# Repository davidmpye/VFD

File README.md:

This repository contains a design for an IV-11 based Vacuum Fluorescent Display (VFD) display unit.

Key points of the design:

* Support for 8 tubes (can install only 6 if you want the traditional 2-2-2 clock display)
* Can daisy chain boards to make longer displays
* Wifi capable (MQTT etc? - firmware doesn't yet enable this)
* Runs off a 5V 2A supply (USB B socket)
* Four buttons for setting time/other functions

Parts count/prices kept down by using 'generic' ebay modules to provide:

* DS3231 Real Time Clock (battery backed)
* Boost converter module to provide the ~25VDC to power the VFD
* Buck converter module to provide 1.5v to heat the cathodes
* Wemos D1 Mini board to provide the brains
* 5mm encapsulated addressable RGB LEDs to provide the colour effects.

Please see the project wiki for more details.

https://github.com/davidmpye/VFD/wiki

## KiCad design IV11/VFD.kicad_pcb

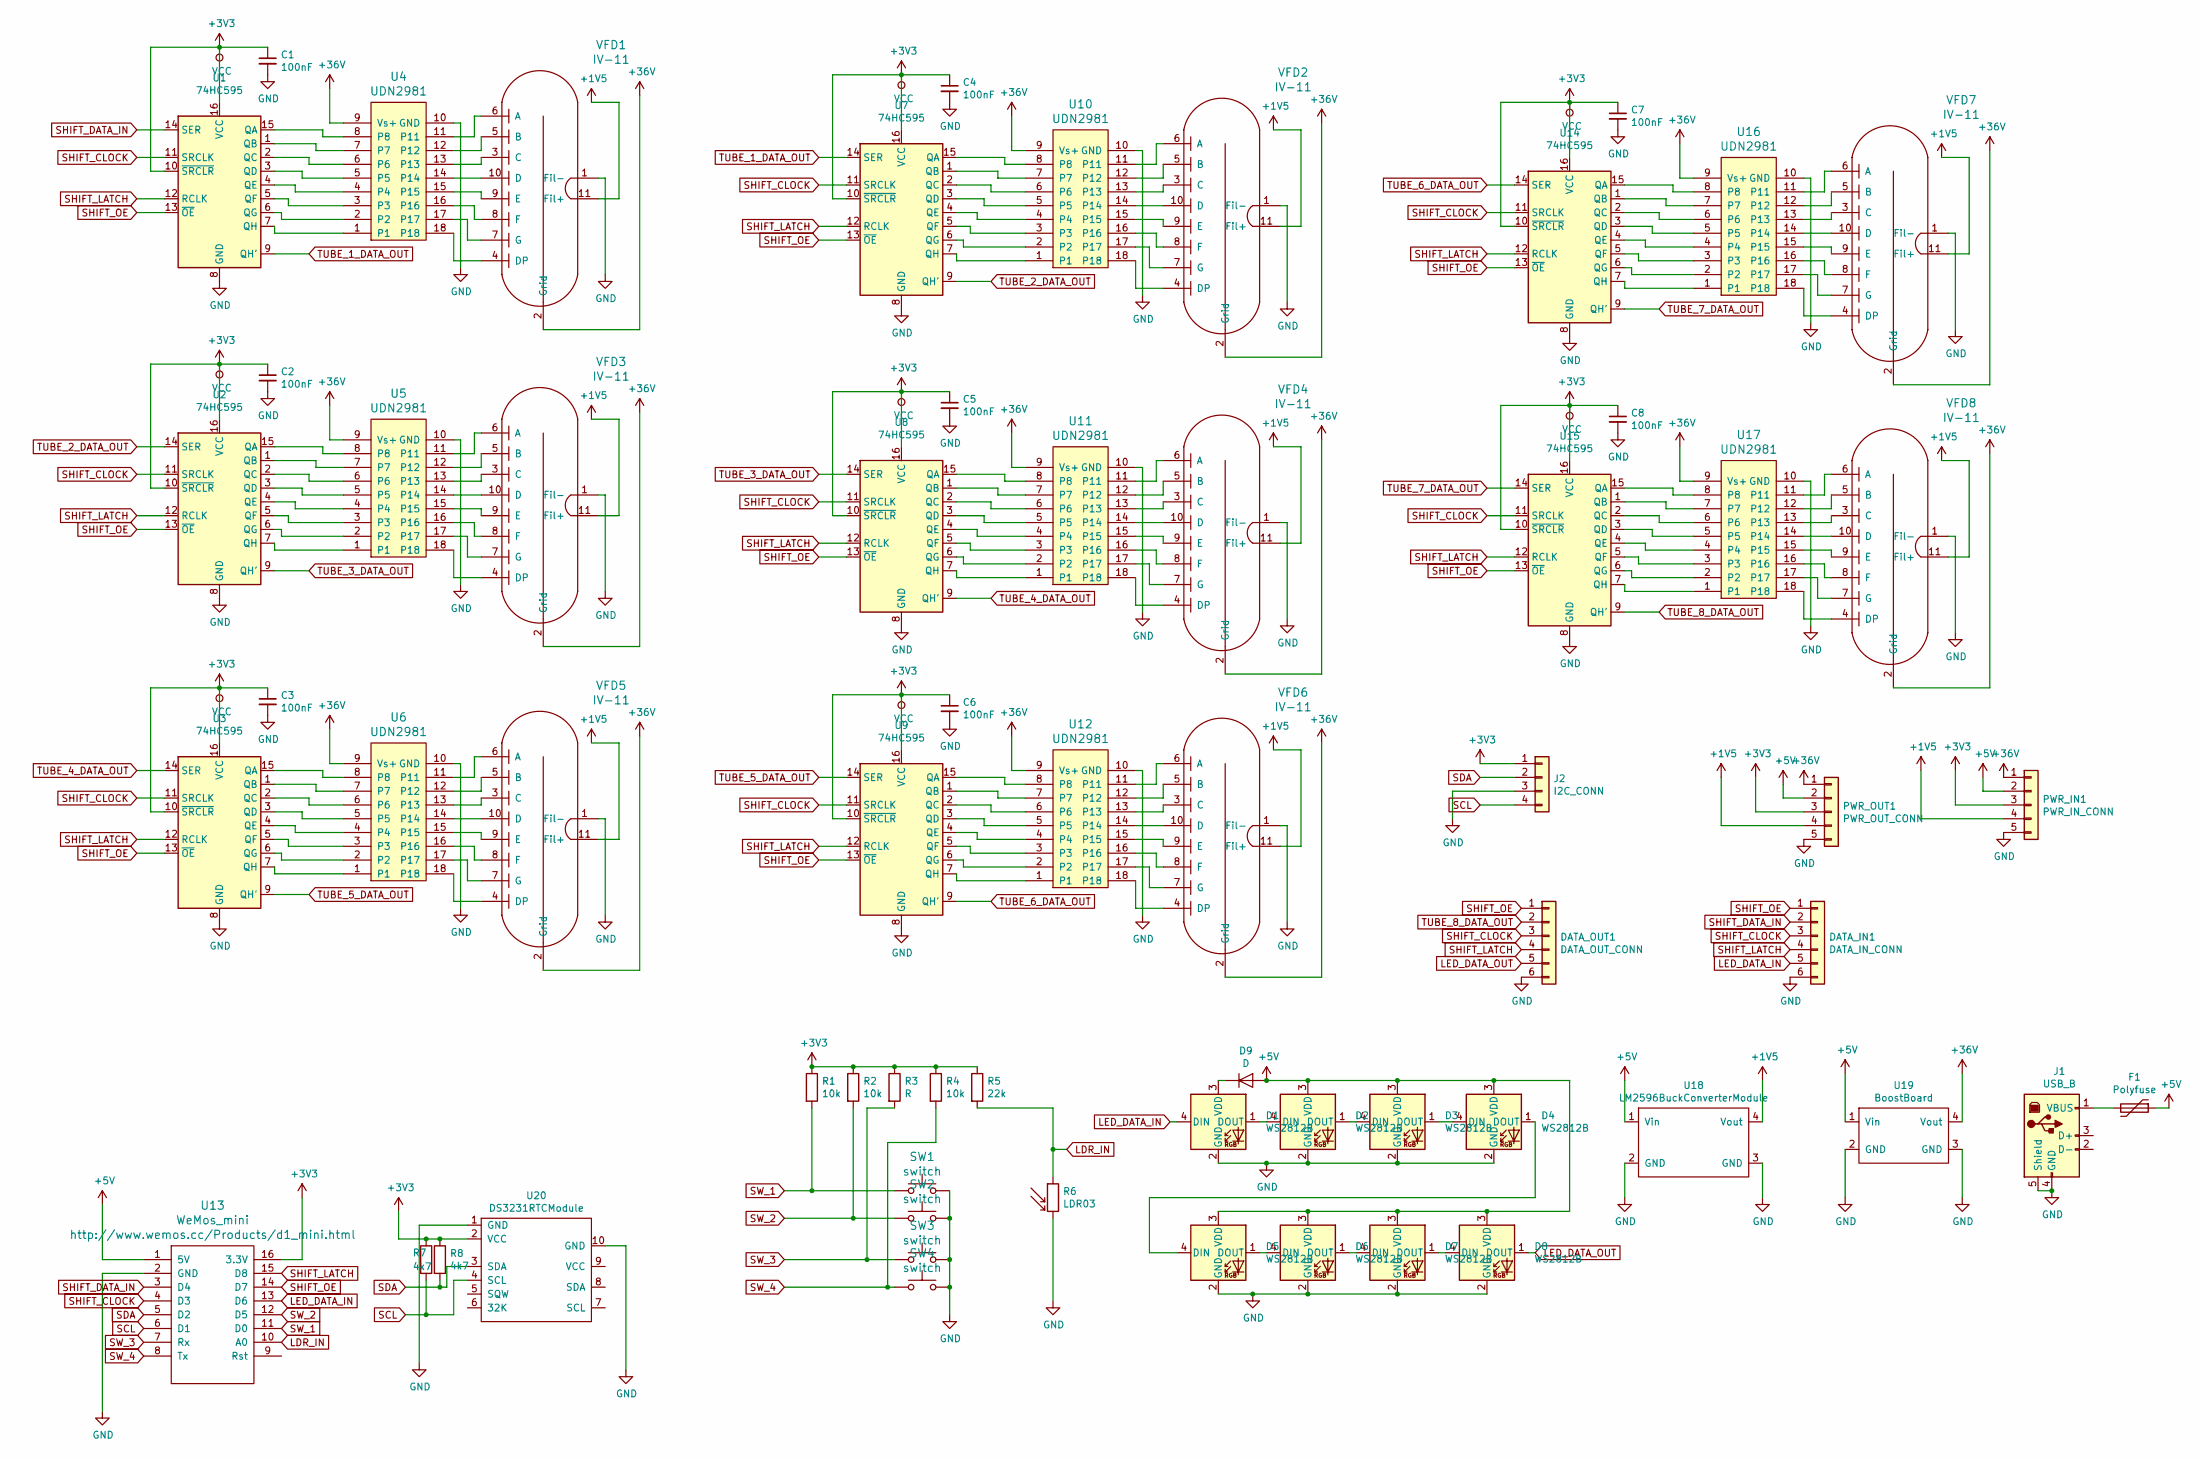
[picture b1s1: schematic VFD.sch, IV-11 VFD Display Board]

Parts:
C1, C2, C3, C4, C5, C6, C7, C8: 100nF; C_Disc_D7.0mm_W2.5mm_P5.00mm
D1, D2, D3, D4, D5, D6, D7, D8: WS2812B; LED_D5.0mm-4-Wide
D9: D; D_DO-35_SOD27_P7.62mm_Horizontal
DATA_IN1: DATA_IN_CONN; PinSocket_1x06_P2.54mm_Horizontal
DATA_OUT1: DATA_OUT_CONN; PinHeader_1x06_P2.54mm_Horizontal
F1: Polyfuse; R_Axial_DIN0309_L9.0mm_D3.2mm_P15.24mm_Horizontal
J1: USB_B; USB_B_OST_USB-B1HSxx_Horizontal
J2: I2C_CONN; PinHeader_1x04_P2.54mm_Horizontal
PWR_IN1: PWR_IN_CONN; PinSocket_1x05_P2.54mm_Horizontal
PWR_OUT1: PWR_OUT_CONN; PinHeader_1x05_P2.54mm_Horizontal
R1, R2, R4: 10k; R_Axial_DIN0411_L9.9mm_D3.6mm_P12.70mm_Horizontal
R3: R; R_Axial_DIN0411_L9.9mm_D3.6mm_P12.70mm_Horizontal
R5: 22k; R_Axial_DIN0411_L9.9mm_D3.6mm_P12.70mm_Horizontal
R6: LDR03; R_LDR_10x8.5mm_P7.6mm_Vertical
R7, R8: 4k7; R_Axial_DIN0411_L9.9mm_D3.6mm_P12.70mm_Horizontal
SW1, SW2, SW3, SW4: switch; SW_Tactile_SKHH_Angled
U1, U2, U3, U7, U8, U9, U14, U15: 74HC595; DIP-16_W7.62mm_Socket_LongPads
U4, U5, U6, U10, U11, U12, U16, U17: UDN2981; DIP-18_W7.62mm_Socket_LongPads
U13: WeMos_mini; D1_mini_board
U18: LM2596BuckConverterModule
U19: BoostBoard; MT3608BoostConverterModule
U20: DS3231RTCModule; DS3121RTCModule
VFD1, VFD2, VFD3, VFD4, VFD5, VFD6, VFD7, VFD8: IV-11

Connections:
+1V5: PWR_IN1.4, PWR_OUT1.4, U18.4 (Vout), VFD1.11 (Fil+), VFD2.11 (Fil+), VFD3.11 (Fil+), VFD4.11 (Fil+), VFD5.11 (Fil+), VFD6.11 (Fil+), VFD7.11 (Fil+), VFD8.11 (Fil+)
+3V3: C1.1, C2.1, C3.1, C4.1, C5.1, C6.1, C7.1, C8.1, J2.1, PWR_IN1.3, PWR_OUT1.3, R1.1, R2.1, R3.1, R4.1, R5.1, R7.1, R8.1, U1.10 (~SRCLR), U1.16 (VCC), U2.10 (~SRCLR), U2.16 (VCC), U3.10 (~SRCLR), U3.16 (VCC), U7.10 (~SRCLR), U7.16 (VCC), U8.10 (~SRCLR), U8.16 (VCC), U9.10 (~SRCLR), U9.16 (VCC), U13.16 (3.3V), U14.10 (~SRCLR), U14.16 (VCC), U15.10 (~SRCLR), U15.16 (VCC), U20.2 (VCC)
+5V: D2.3 (VDD), D3.3 (VDD), D4.3 (VDD), D5.3 (VDD), D6.3 (VDD), D7.3 (VDD), D8.3 (VDD), D9.2 (A), F1.1, PWR_IN1.2, PWR_OUT1.2, U13.1 (5V), U18.1 (Vin), U19.1 (Vin)
+36V: PWR_IN1.1, PWR_OUT1.1, U4.9 (Vs+), U5.9 (Vs+), U6.9 (Vs+), U10.9 (Vs+), U11.9 (Vs+), U12.9 (Vs+), U16.9 (Vs+), U17.9 (Vs+), U19.4 (Vout), VFD1.2 (Grid), VFD2.2 (Grid), VFD3.2 (Grid), VFD4.2 (Grid), VFD5.2 (Grid), VFD6.2 (Grid), VFD7.2 (Grid), VFD8.2 (Grid)
GND: C1.2, C2.2, C3.2, C4.2, C5.2, C6.2, C7.2, C8.2, D1.2 (GND), D2.2 (GND), D3.2 (GND), D4.2 (GND), D5.2 (GND), D6.2 (GND), D7.2 (GND), D8.2 (GND), DATA_IN1.6, DATA_OUT1.6, J1.4 (GND), J1.5 (Shield), J2.3, PWR_IN1.5, PWR_OUT1.5, R6.2, SW1.2, SW2.2, SW3.2, SW4.2, U1.8 (GND), U2.8 (GND), U3.8 (GND), U4.10 (GND), U5.10 (GND), U6.10 (GND), U7.8 (GND), U8.8 (GND), U9.8 (GND), U10.10 (GND), U11.10 (GND), U12.10 (GND), U13.2 (GND), U14.8 (GND), U15.8 (GND), U16.10 (GND), U17.10 (GND), U18.2 (GND), U18.3 (GND), U19.2 (GND), U19.3 (GND), U20.1 (GND), U20.10 (GND), VFD1.1 (Fil-), VFD2.1 (Fil-), VFD3.1 (Fil-), VFD4.1 (Fil-), VFD5.1 (Fil-), VFD6.1 (Fil-), VFD7.1 (Fil-), VFD8.1 (Fil-)
LDR_IN: R5.2, R6.1, U13.10 (A0)
LED_DATA_IN: D1.4 (DIN), DATA_IN1.5, U13.13 (D6)
LED_DATA_OUT: D8.1 (DOUT), DATA_OUT1.5
unnamed: D1.1 (DOUT), D2.4 (DIN)
unnamed: D1.3 (VDD), D9.1 (K)
unnamed: D2.1 (DOUT), D3.4 (DIN)
unnamed: D3.1 (DOUT), D4.4 (DIN)
unnamed: D4.1 (DOUT), D5.4 (DIN)
unnamed: D5.1 (DOUT), D6.4 (DIN)
unnamed: D6.1 (DOUT), D7.4 (DIN)
unnamed: D7.1 (DOUT), D8.4 (DIN)
unnamed: F1.2, J1.1 (VBUS)
unnamed: U1.1 (QB), U4.7
unnamed: U1.2 (QC), U4.6
unnamed: U1.3 (QD), U4.5
unnamed: U1.4 (QE), U4.4
unnamed: U1.5 (QF), U4.3
unnamed: U1.6 (QG), U4.2
unnamed: U1.7 (QH), U4.1
unnamed: U1.15 (QA), U4.8
unnamed: U2.1 (QB), U5.7
unnamed: U2.2 (QC), U5.6
unnamed: U2.3 (QD), U5.5
unnamed: U2.4 (QE), U5.4
unnamed: U2.5 (QF), U5.3
unnamed: U2.6 (QG), U5.2
unnamed: U2.7 (QH), U5.1
unnamed: U2.15 (QA), U5.8
unnamed: U3.1 (QB), U6.7
unnamed: U3.2 (QC), U6.6
unnamed: U3.3 (QD), U6.5
unnamed: U3.4 (QE), U6.4
unnamed: U3.5 (QF), U6.3
unnamed: U3.6 (QG), U6.2
unnamed: U3.7 (QH), U6.1
unnamed: U3.15 (QA), U6.8
unnamed: U4.11, VFD1.6 (A)
unnamed: U4.12, VFD1.5 (B)
unnamed: U4.13, VFD1.3 (C)
unnamed: U4.14, VFD1.10 (D)
unnamed: U4.15, VFD1.9 (E)
unnamed: U4.16, VFD1.8 (F)
unnamed: U4.17, VFD1.7 (G)
unnamed: U4.18, VFD1.4 (DP)
unnamed: U5.11, VFD3.6 (A)
unnamed: U5.12, VFD3.5 (B)
unnamed: U5.13, VFD3.3 (C)
unnamed: U5.14, VFD3.10 (D)
unnamed: U5.15, VFD3.9 (E)
unnamed: U5.16, VFD3.8 (F)
unnamed: U5.17, VFD3.7 (G)
unnamed: U5.18, VFD3.4 (DP)
unnamed: U6.11, VFD5.6 (A)
unnamed: U6.12, VFD5.5 (B)
unnamed: U6.13, VFD5.3 (C)
unnamed: U6.14, VFD5.10 (D)
unnamed: U6.15, VFD5.9 (E)
unnamed: U6.16, VFD5.8 (F)
unnamed: U6.17, VFD5.7 (G)
unnamed: U6.18, VFD5.4 (DP)
unnamed: U7.7 (QH), U10.1
unnamed: U7.6 (QG), U10.2
unnamed: U7.5 (QF), U10.3
unnamed: U7.4 (QE), U10.4
unnamed: U7.3 (QD), U10.5
unnamed: U7.2 (QC), U10.6
unnamed: U7.1 (QB), U10.7
unnamed: U7.15 (QA), U10.8
unnamed: U10.11, VFD2.6 (A)
unnamed: U10.12, VFD2.5 (B)
unnamed: U10.13, VFD2.3 (C)
unnamed: U10.14, VFD2.10 (D)
unnamed: U10.15, VFD2.9 (E)
unnamed: U10.16, VFD2.8 (F)
unnamed: U10.17, VFD2.7 (G)
unnamed: U10.18, VFD2.4 (DP)
unnamed: U8.7 (QH), U11.1
unnamed: U8.6 (QG), U11.2
unnamed: U8.5 (QF), U11.3
unnamed: U8.4 (QE), U11.4
unnamed: U8.3 (QD), U11.5
unnamed: U8.2 (QC), U11.6
unnamed: U8.1 (QB), U11.7
unnamed: U8.15 (QA), U11.8
unnamed: U11.11, VFD4.6 (A)
unnamed: U11.12, VFD4.5 (B)
unnamed: U11.13, VFD4.3 (C)
unnamed: U11.14, VFD4.10 (D)
unnamed: U11.15, VFD4.9 (E)
unnamed: U11.16, VFD4.8 (F)
unnamed: U11.17, VFD4.7 (G)
unnamed: U11.18, VFD4.4 (DP)
unnamed: U9.7 (QH), U12.1
unnamed: U9.6 (QG), U12.2
unnamed: U9.5 (QF), U12.3
unnamed: U9.4 (QE), U12.4
unnamed: U9.3 (QD), U12.5
unnamed: U9.2 (QC), U12.6
unnamed: U9.1 (QB), U12.7
unnamed: U9.15 (QA), U12.8
unnamed: U12.11, VFD6.6 (A)
unnamed: U12.12, VFD6.5 (B)
unnamed: U12.13, VFD6.3 (C)
unnamed: U12.14, VFD6.10 (D)
unnamed: U12.15, VFD6.9 (E)
unnamed: U12.16, VFD6.8 (F)
unnamed: U12.17, VFD6.7 (G)
unnamed: U12.18, VFD6.4 (DP)
unnamed: U14.1 (QB), U16.7
unnamed: U14.2 (QC), U16.6
unnamed: U14.3 (QD), U16.5
unnamed: U14.4 (QE), U16.4
unnamed: U14.5 (QF), U16.3
unnamed: U14.6 (QG), U16.2
unnamed: U14.7 (QH), U16.1
unnamed: U14.15 (QA), U16.8
unnamed: U15.1 (QB), U17.7
unnamed: U15.2 (QC), U17.6
unnamed: U15.3 (QD), U17.5
unnamed: U15.4 (QE), U17.4
unnamed: U15.5 (QF), U17.3
unnamed: U15.6 (QG), U17.2
unnamed: U15.7 (QH), U17.1
unnamed: U15.15 (QA), U17.8
unnamed: U16.11, VFD7.6 (A)
unnamed: U16.12, VFD7.5 (B)
unnamed: U16.13, VFD7.3 (C)
unnamed: U16.14, VFD7.10 (D)
unnamed: U16.15, VFD7.9 (E)
unnamed: U16.16, VFD7.8 (F)
unnamed: U16.17, VFD7.7 (G)
unnamed: U16.18, VFD7.4 (DP)
unnamed: U17.11, VFD8.6 (A)
unnamed: U17.12, VFD8.5 (B)
unnamed: U17.13, VFD8.3 (C)
unnamed: U17.14, VFD8.10 (D)
unnamed: U17.15, VFD8.9 (E)
unnamed: U17.16, VFD8.8 (F)
unnamed: U17.17, VFD8.7 (G)
unnamed: U17.18, VFD8.4 (DP)
SCL: J2.4, R7.2, U13.6 (D1), U20.4 (SCL)
SDA: J2.2, R8.2, U13.5 (D2), U20.3 (SDA)
SHIFT_CLOCK: DATA_IN1.3, DATA_OUT1.3, U1.11 (SRCLK), U2.11 (SRCLK), U3.11 (SRCLK), U7.11 (SRCLK), U8.11 (SRCLK), U9.11 (SRCLK), U13.4 (D3), U14.11 (SRCLK), U15.11 (SRCLK)
SHIFT_DATA_IN: DATA_IN1.2, U1.14 (SER), U13.3 (D4)
SHIFT_LATCH: DATA_IN1.4, DATA_OUT1.4, U1.12 (RCLK), U2.12 (RCLK), U3.12 (RCLK), U7.12 (RCLK), U8.12 (RCLK), U9.12 (RCLK), U13.15 (D8), U14.12 (RCLK), U15.12 (RCLK)
SHIFT_OE: DATA_IN1.1, DATA_OUT1.1, U1.13 (~OE), U2.13 (~OE), U3.13 (~OE), U7.13 (~OE), U8.13 (~OE), U9.13 (~OE), U13.14 (D7), U14.13 (~OE), U15.13 (~OE)
SW_1: R1.2, SW1.1, U13.11 (D0)
SW_2: R2.2, SW2.1, U13.12 (D5)
SW_3: R3.2, SW3.1, U13.7 (Rx)
SW_4: R4.2, SW4.1, U13.8 (Tx)
TUBE_1_DATA_OUT: U1.9 (QH'), U7.14 (SER)
TUBE_2_DATA_OUT: U2.14 (SER), U7.9 (QH')
TUBE_3_DATA_OUT: U2.9 (QH'), U8.14 (SER)
TUBE_4_DATA_OUT: U3.14 (SER), U8.9 (QH')
TUBE_5_DATA_OUT: U3.9 (QH'), U9.14 (SER)
TUBE_6_DATA_OUT: U9.9 (QH'), U14.14 (SER)
TUBE_7_DATA_OUT: U14.9 (QH'), U15.14 (SER)
TUBE_8_DATA_OUT: DATA_OUT1.2, U15.9 (QH')

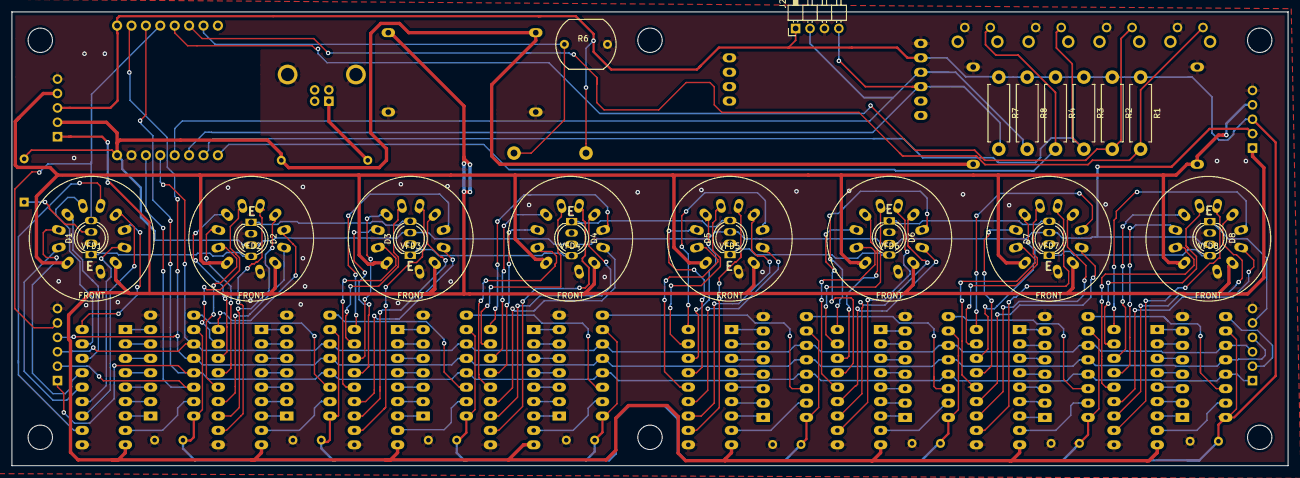
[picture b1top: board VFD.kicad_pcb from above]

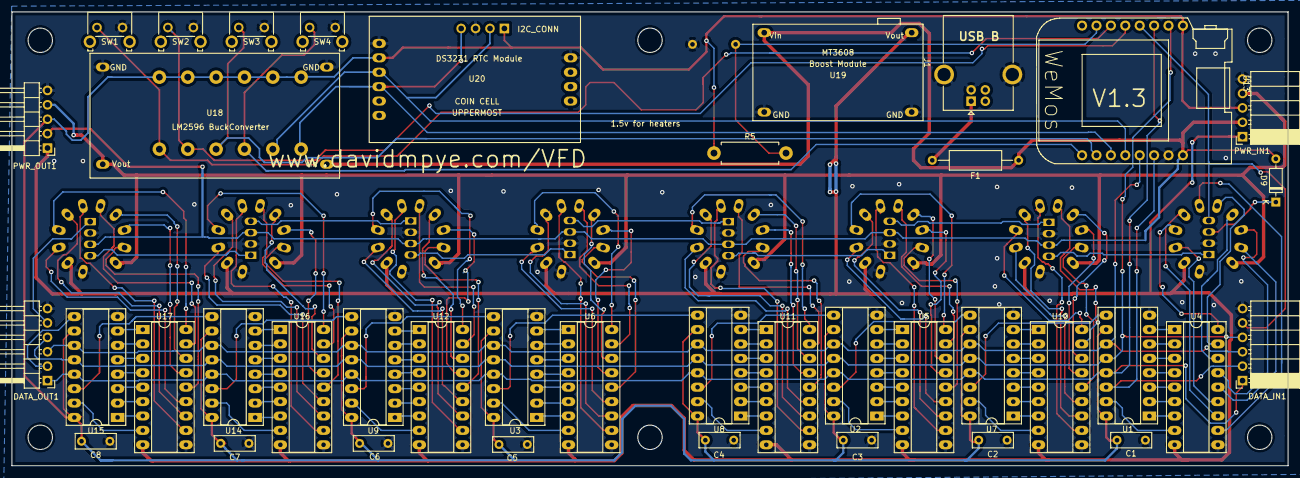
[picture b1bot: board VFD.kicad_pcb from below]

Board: 2 copper layers, 225.0 x 80.0 mm, 64 parts (40 on the bottom side), 163 nets.

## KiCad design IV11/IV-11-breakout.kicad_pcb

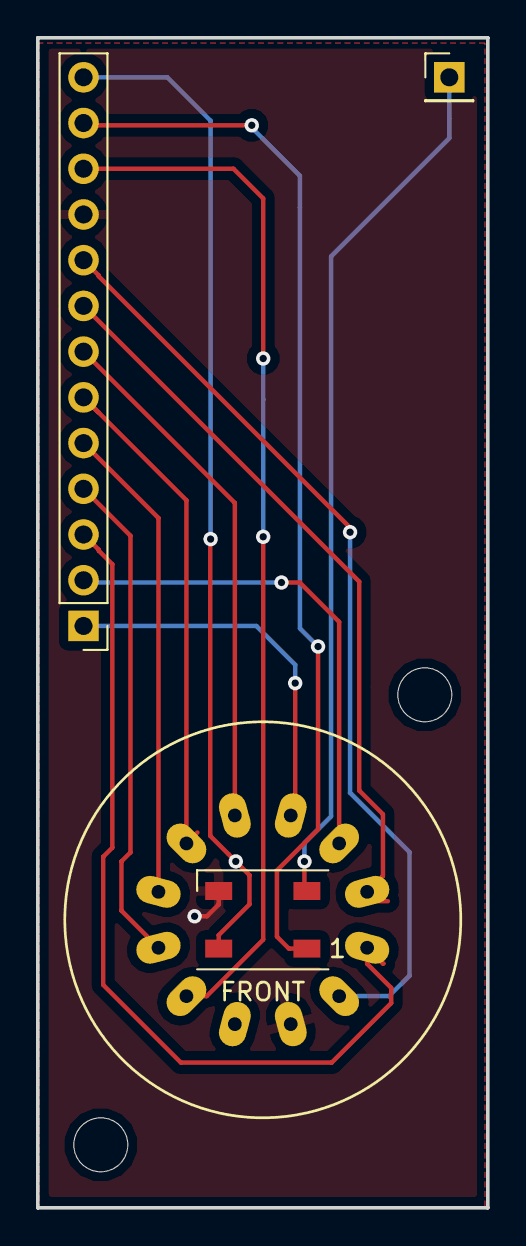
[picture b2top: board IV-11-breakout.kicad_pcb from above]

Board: 2 copper layers, 25.0 x 65.0 mm, 4 parts (0 on the bottom side), 14 nets.

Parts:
D1: WS2812B; LED_WS2812B_PLCC4_5.0x5.0mm_P3.2mm
J1: Conn_01x13_Male; PinHeader_1x13_P2.54mm_Vertical
J2: Conn_01x01; PinHeader_1x01_P2.54mm_Vertical
VFD1: IV-11

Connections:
/A: J1.1, VFD1.6
/B: J1.2, VFD1.5
/C: J1.3, VFD1.3
/D: J1.4, VFD1.10
/DP: J1.8, VFD1.4
/E: J1.5, VFD1.9
/F: J1.6, VFD1.8
/G: J1.7, VFD1.7
/GRID: J1.9, VFD1.2
/HEATER+V: J1.11, VFD1.11
/LED+V: D1.1, J1.12
/LED_DIN: D1.4, J1.13
/LED_DOUT: D1.2, J2.1
GND: D1.3, J1.10, VFD1.1

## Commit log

2018-06-05 Initial import
2018-06-05 Initial import of 3d printed model for tube base mount
2018-06-07 Tweaks!
2018-06-07 Further updates!
2018-06-07 Tweak silkscreen
2018-06-07 Redone without the resistor
2018-06-07 Make walls thinner
2018-06-07 Further tweaks to 3d printed base
2018-07-20 Change to make base much thicker to take a 5mm 'encapsulated' neopixel
2018-07-25 Initial push of IV11 modular clock design
2018-08-02 Make base thicker
2018-08-02 Import kicad cache
2018-08-02 Fix back to front LEDs
2018-08-02 Changes for back to front LED markings
2018-08-02 UDN2981-THT schematic added
2018-08-02 5mm neopixel schematic added
2018-08-02 Fix footpring mistakes
2018-08-02 Update footprints to use the 'generic modules'
2018-08-02 Finish import of new neopixel footprint and associated groundfill changes
2018-08-07 Redesign tube base so it is in two halves, with interlocking lugs. Reason: Without a splittable removable base, replacing the tubes are almost impossible!
2018-08-07 Updates to use further-spaced LED footprints for the 5mm neopixels to make rework easier!
2018-08-07 Fixes for not using D0 for the LEDs...
2018-08-08 Make LED footprint pads slightly narrower (1.3mm) for easier solderingx
2018-08-08 Add wide-space-led footprint
2018-08-08 s/chinesemodules/genericmodules
2018-08-08 PCB updates - rerouted track for 3v3 to shift registers and refilled ground planes accordingly
2018-08-08 V1.1 board completed, + gerbers
2018-08-12 Add Openscad design for the clock case
2018-08-12 Slight tweak to hole positions
2018-08-24 Adjust cutout holes (again!) for USB hole and the push buttons
2018-08-28 Add LDR hole
2018-09-19 Add the initial draft of the software
2018-09-19 Tidying
2018-11-01 Fix bug for switches not being connected to ground!
2018-11-01 Fix problems with switches not being connected to ground
2018-11-01 Update version number (now 1.2). Sigh.
2018-11-01 Add JC_Button library - it's excellent
2018-11-02 Import of button handling code - you can now set the time!
2018-11-02 Fix the AMPM display mode bug
2018-11-02 Tweaks to button layouts
2018-11-02 Now with working button C to select LED colour modes
2018-11-07 Updates to config and button handler - largely reordering functions
2018-11-07 Reordering display driver code and adding comments
2018-11-12 Fix order for setting time->date, and button responsiveness
2018-11-13 Add in test mode with long press on button D to display all segments on all tubes
2018-11-14 Adjust shell to fit together better
2018-11-14 Change LDR resistor val to 22k
2018-11-14 Minor tweaks
2018-11-17 Remove OSHW logo - unfortunately with the generic modules, we can't meet OSHW requirements
2018-11-17 Final updates to complete PCB revision 1.2 including an I2C breakout connector
2018-11-17 Re-added gerbers.zip for the 1.2 gerbers
2018-11-17 Add the rest of the kicad project files
2018-11-17 Fix missing } (thanks Jon!)
2018-11-19 Add a long-press of button 3 to display the hex readout from the LDR. Also, recalibrate the LDR readouts for a 22k series resistor
2018-11-20 Add a displayInt option to the display class Brightness to adjust in small steps towards desired brightness.
2018-11-21 Multiple fixes to graduated dimming, and allow the LEDs to be turned off at low brightness settings
2018-11-21 Annoying flicker fix
2018-11-21 Whitespace adjusts
2018-11-21 Minor tweak to tube position
2018-11-21 Fix brightness issue (AGAIN)
2018-11-21 Adjust the test() routine to apply the decimal point also
2018-11-22 Add GPLv3.0 boilerplate
2018-11-22 Add licence file
2018-11-23 Make adjustments for front mounted LDR
2018-11-23 Add DXF of clock case for non-laser cutter peeps
2018-11-23 Tweaks to LDR hole
2018-11-25 Hopefully fix alignment issue with top cover
2018-11-25 More antiflicker and anti LED glitching
2018-11-26 More work to stop flickering and flashing (especially at low brightness levels)
2018-11-27 Try increasing the PWM frequency to 400Hz to reduce flicker, and reenable interrupts as it's causing crashes
2018-11-27 Flicker-fix again
2018-11-28 More flicker fixes!
2018-11-30 More antiflicker updates, and update to use the latest arduino core from github, which fixes a number of flicker related issues
2018-11-30 Add the FASTLED interrupt disabler again
2018-11-30 Make 3d printed base hole a bit larger for easier fitting
2018-11-30 Refactoring of update()
2018-12-01 Cap analogread values
2018-12-01 Rename variable to aid intuitiveness
2018-12-05 Final tweaks to case
2018-12-05 Spacers if wanted
2018-12-08 Add code to Display to enable dashes() on time mode if wanted...
2018-12-08 Tweak for only applying dashes in AMPM/24hr mode
2018-12-12 Fix NSR's reported bug with date entry
2019-02-21 Stealth and Col By Tikme modes added
    Stealth Mode = no LEDs on
    Col By Time = Colours based on Hours, Minutes and Seconds.
2019-02-21 Stalth Mode fixed
    Stealth Mode fixed so LEDs turn off if they are already on.
2019-02-22 Hello message added
    Hello message added
2019-02-22 Few syntax tweaks
2019-02-22 Scrolling Hello welcome message added
2019-02-23 Changes to synchronise tube numbering to match LED numbering - ie 0 is the leftmost tube
2019-02-23 Fix for merge now tubes are renumbered
2019-02-23 Another fix needed for tube renumbering
2019-02-23 Another fix!
2019-02-23 Multiple fixes to sort out 6 and 8 tube clock options
2019-02-24 Oops, changed default tube number
2019-02-26 Add: 1) Multiple WiFi APs 2) NTP support
2019-02-27 1) Remove NTPClient symlink from /lib, 2) Add NtpClientLib to lib_deps, 3) Add comments, 4) Show connected AP, 5) Fix DP's code ('FF' fault display), 6) Fix my code (unblock clock from starting when 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
2019-02-27 Just a merge of a separate client, no biggie.
2019-02-27 Hello message fixed and fonts annotated
2019-02-27 Start of adding WiFiManager feature.
2019-02-27 Add WifiManager to list of libdeps
2019-02-28 Speedier startup, especially if you aren't using Wifi
2019-02-28 Stashy mcStashFace.
2019-03-01 Added https://github.com/tzapu/WiFiManager
2019-03-02 Ascii font and message scroller added
2019-03-03 Stealth Mode improved in bright conditions
    Stealth Mode changed so LEDs do not update in bright conditions
2019-03-06 1) Beginnings of a simple web server (currently a 'Hello World'), 2) Settings saved to SPIFFS as config.json.
2019-03-06 Merged
2019-03-06 Remove two IPChar display calls that didn't work
2019-03-06 Fixes to make date display work properly on 8 tubes Fixes to make it possible to set date/time with Iain's new API
2019-03-06 Make the scrollmessage function able to handle C strings
2019-03-06 Improve the test function
2019-03-11 Access Point Setup feature added.
2019-03-12 IP address display improvements, Wifi-related code tidying & improvements, Added comments.
2019-03-20 Add letter labels to the buttons
2019-03-20 Fix the bug in 12 hour display mode
2019-03-20 Further fix to 12 hour mode
2019-03-21 Add precompiled firmware binary
2019-03-21 8 tube firmware upload
2019-03-21 Precompiled firmware binaries for 6 and 8 tube versions
2019-03-21 Oops, bugged firmware!
2019-03-21 Fix regression in buttonhandler which broke time and date setting again
2019-04-15 Fixed short vs long button press gesture code.
2019-04-15 Fixed short vs long button press gesture code in ButtonHandler.
2019-04-17 Fix button press saves, Update webserver config page.
2019-04-21 Import initial filesystem for the web interface
2019-04-21 Major refactoring (still in progress!) for the websockets UI
2019-04-21 Removing of bits of handler
2019-04-21 More helpful 404 message
2019-04-21 Further tweaks
2019-04-21 Now working (and with working OTA update)
2019-04-21 Re-insert the fix for LED flickering, now the ESP8266 Arduino Core has started using NMI for PWM (again). Sigh.x
2019-04-21 Further work on webUI
2019-04-22 Lots of refactoring for webui
2019-04-25 Multiple new changes, still alpha quality at present
2019-04-25 Make holding button 1+2 reset the config settings
2019-04-25 Refactoring of the display class to make it more readable and in preparation for transitions
2019-04-25 No need to use the 'bleeding edge'
2019-04-25 Oops, actually unless you like to live in flickerland, we do
2019-04-25 Major reengineering again, config is now stored in a global struct, which configmanager will be able to read and write to JSON file
2019-04-25 Small fix
2019-04-26 Numerous changes to make the configmanager do its' work, and make the webhandler prepopulate button fields for different pages
2019-04-28 Tweaks to load welcome message from config
2019-04-29 Further changes to configmanager and display classes to improve integration with the config object
2019-04-30 Change back to the release version of the 8266 environment
2019-04-30 Initial work towards storing and loading wifi settings in the config flie
2019-04-30 Web dev
2019-04-30 Initial draft import of wifi config page
2019-05-01 Pare back the web interface, start to implement more functionality
2019-05-01 Fix broken display->test()
2019-05-01 Fix test() again!
2019-05-04 Remove the NTPclient libdep as it won't build at the moment! Go back to the 'stage' version of ESP8266 core. Add mDNS support to the code (but not yet the web UI)
2019-05-04 Changes to allow welcome message to be set via webui
2019-05-05 Display message to confirm reset
2019-05-05 Fix MDNS so it works!
2019-05-05 Further updates, mostly for wifi
2019-05-05 Remove the dumpConfig
2019-05-05 Initial work to support time setting
2019-05-06 Now auto-reflash the default configuration if the format has changed
2019-05-06 Fix problem with softAP
2019-05-06 Dim fixes
2019-05-06 Add -s for displaying date on 8 tube clocks
2019-11-05 Add barbs for tube bases
2019-11-05 IV11 bases x8 as 3mf file
2019-11-06 Add STL file for tube base for people without OpenSCAD
2019-11-13 Major redesign to use different buck converter, and also up-rate track thickness for power rails
2019-11-13 Add in room for polyfuse
2019-11-13 Update thickness of 48VDC tracks x
2019-11-20 Change design to use 3dprinted spacers
2019-11-20 Make top spacers a bit thicker
2019-11-28 Update spacer length
2019-11-30 Fix issue with RTC not being formally initialised
2019-11-30 Multiple retries to init RTC before giving up
2019-12-01 Remove Wire.begin, because rtc.begin calls it again anyway
2019-12-28 Tidy leaft over intermediate files
    Add ignore rules for KiCad temporary files and rmeove those left behind.
2025-01-25 Web Handler dropped and NTP added
2025-01-25 Unnecessary includes removed.
